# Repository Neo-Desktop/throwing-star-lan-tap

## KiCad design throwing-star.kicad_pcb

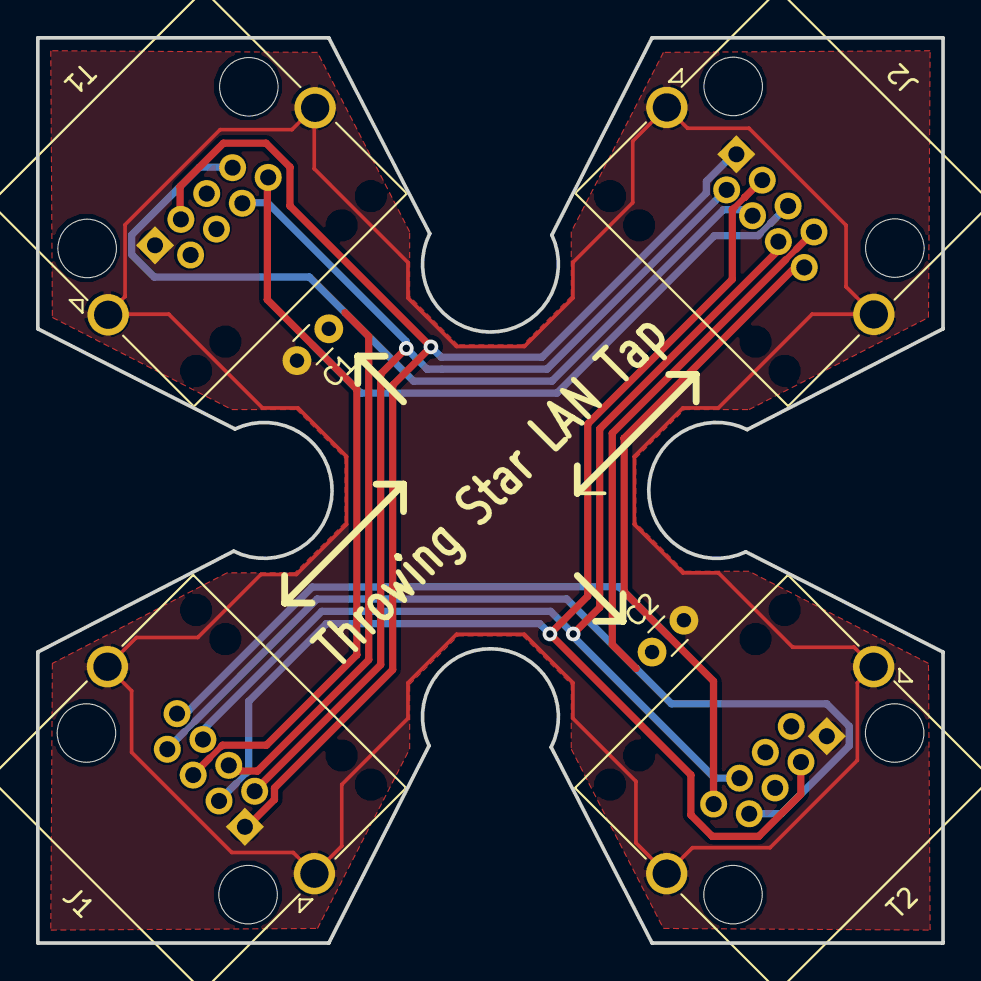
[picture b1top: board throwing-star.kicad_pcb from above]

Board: 2 copper layers, 50.3 x 50.3 mm, 6 parts (0 on the bottom side), 9 nets.

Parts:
C1, C2: 220pF; C_Disc_D3.0mm_W1.6mm_P2.50mm
J1, J2: RJ45; RJ45_Amphenol_RJHSE5380
T1, T2: RJ45; RJ45_Amphenol_RJHSE5380

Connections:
/SIG1: J1.1, J2.1, T1.3
/SIG2: J1.2, J2.2, T1.6
/SIG3: J1.3, J2.3, T2.3
/SIG4: C1.1, J1.4, J2.4, T1.7
/SIG5: C1.2, J1.5, J2.5, T1.8
/SIG6: J1.6, J2.6, T2.6
/SIG7: C2.1, J1.7, J2.7, T2.7
/SIG8: C2.2, J1.8, J2.8, T2.8
GND: J1.SH, J2.SH, T1.SH, T2.SH

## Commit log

2020-07-23 update project using kicad (5.1.6)-1
